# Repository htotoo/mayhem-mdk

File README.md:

# PortaPack Mayhem External Module Developer Kit "MDK"
This is the Developer Kit External Module for the [HackRF+PortaPack H4](https://github.com/portapack-mayhem/mayhem-firmware)

## How to get the hardware
All the design files are in the pcb folder. They are set up so you can let [JLCPCB](https://jlcpcb.com/) manufacture a few boards by using the files in pcb/production.

## How to compile
The software consists of two separate parts:
- The Standalone App that is uploaded and executed on the portapack.
  - This will be embedded in the the ESP32 firmware, so is required first.
  - The guide can be found [here](src/uart/Readme.md)
- The firmware for the ESP32-S3.
  - The guide can be found [here](src/portapack-external-module/README.md) 
  - Note: ESP-IDF version 5.4 introduced a breaking change in the I2C subsystem. So use the latest version of 5.3.

## How to use the example UART app
Once the Firmware is uploaded and the module is plugged into the Portapack, the UART app should appear in the Utilities menu.

The UART app will display any UART signal on pin 14.

## Schematics

## Pinout

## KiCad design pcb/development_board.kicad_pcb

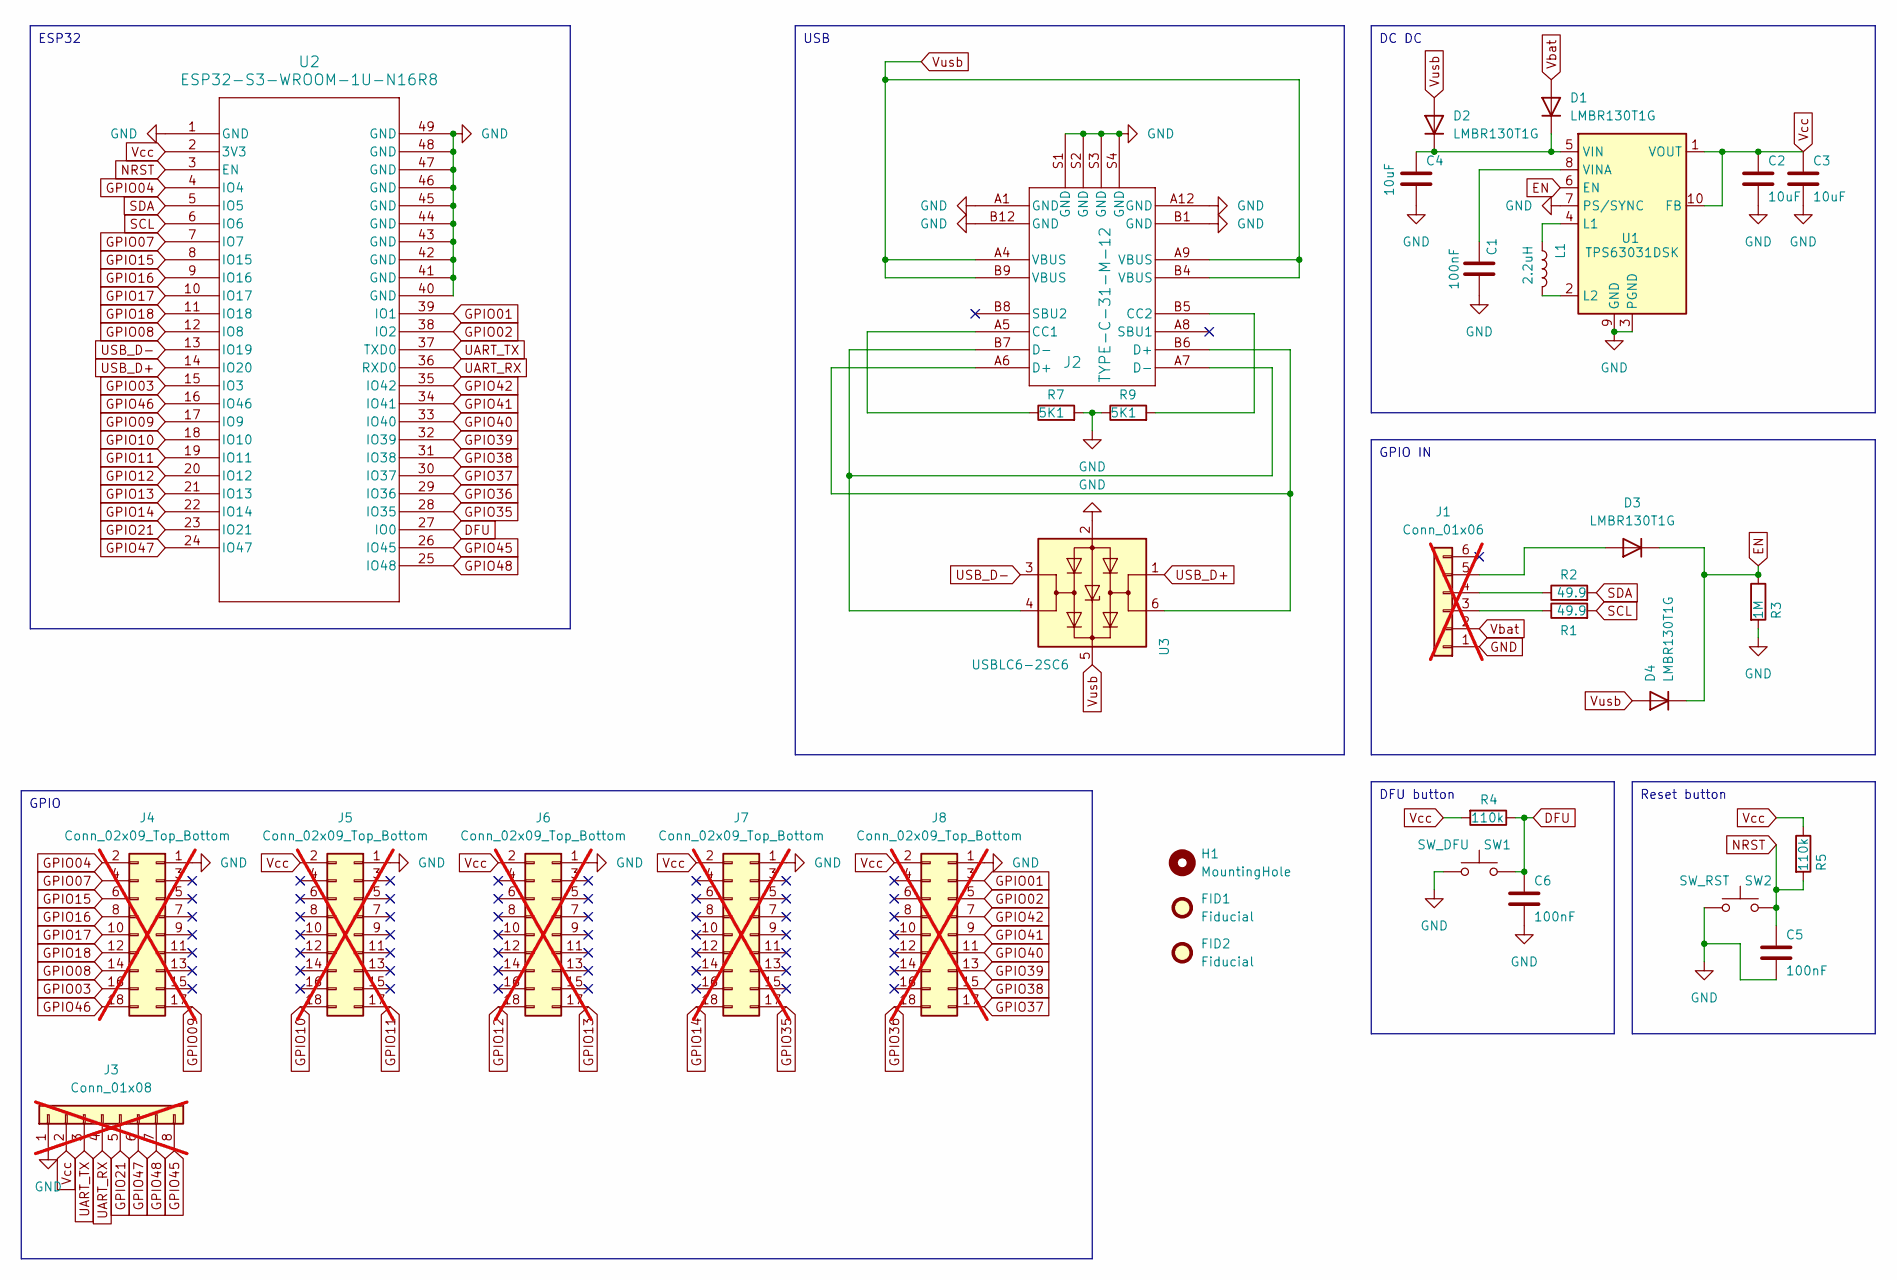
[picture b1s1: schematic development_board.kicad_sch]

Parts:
C1, C5, C6: 100nF; C_0402_1005Metric; Part CL05B104KO5NNNC; JLC 0402
C2, C3, C4: 10uF; C_0402_1005Metric; Part CL05A106MQ5NUNC; JLC 0402
D1, D2, D3, D4: LMBR130T1G; D_SOD-123; Part LMBR130T1G; JLC SOD-123
FID1, FID2: Fiducial; Fiducial_0.75mm_Mask1.5mm
H1: MountingHole; MountingHole_2mm
J1: Conn_01x06; External Module; not fitted
J2: TYPE-C-31-M-12; JLC SMD
J3: Conn_01x08; PinSocket_1x08_P2.54mm_Vertical; not fitted
J4, J5, J6, J7, J8: Conn_02x09_Top_Bottom; PinSocket_2x09_P2.54mm_Vertical; not fitted
L1: 2.2uH; L_Taiyo-Yuden_NR-40xx; Part NRS4010T2R2MDGGV; JLC SMD,4x4mm
R1, R2: 49.9; R_0402_1005Metric; Part 0402WGF499JTCE; JLC 0402
R3: 1M; R_0603_1608Metric; Part 0603WAF1004T5E; JLC 0603
R4, R5: 110k; R_0603_1608Metric; Part 0603WAF1103T5E; JLC 0603
R7, R9: 5K1; R_0603_1608Metric; Part 0603WAF5101T5E; JLC 0603
SW1: SW_DFU; SW_Push_1P1T_XKB_TS-1187A; Part TS-1187A-B-A-B; JLC SMD
SW2: SW_RST; SW_Push_1P1T_XKB_TS-1187A; Part TS-1187A-B-A-B; JLC SMD
U1: TPS63031DSK; WSON-10-1EP_2.5x2.5mm_P0.5mm_EP1.2x2mm; Part TPS63031DSKR; JLC SON-10-EP(2.5x2.5)
U2: ESP32-S3-WROOM-1U-N16R8; ESP32­S3­WROOM­1U_EXP; Part ESP32-S3-WROOM-1U-N16R8; JLC SMD,18x19.2mm
U3: USBLC6-2SC6; SOT-23-6; Part USBLC6-2SC6; JLC SOT-23-6

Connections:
DFU: C6.1, R4.1, SW1.2, U2.27 (IO0)
EN: D3.1 (K), D4.1 (K), R3.1, U1.6 (EN)
GND: C1.2, C2.2, C3.2, C4.2, C5.2, C6.2, J1.1, J2.A1 (GND), J2.A12 (GND), J2.B1 (GND), J2.B12 (GND), J2.S1 (GND), J2.S2 (GND), J2.S3 (GND), J2.S4 (GND), J3.1, J4.1, J5.1, J6.1, J7.1, J8.1, R3.2, R7.2, R9.1, SW1.1, SW2.1, U1.3 (PGND), U1.7 (PS/SYNC), U1.9 (GND), U1.11 (PGND), U2.1 (GND), U2.40 (GND), U2.41 (GND), U2.42 (GND), U2.43 (GND), U2.44 (GND), U2.45 (GND), U2.46 (GND), U2.47 (GND), U2.48 (GND), U2.49 (GND), U3.2 (GND)
GPIO01: J8.3, U2.39 (IO1)
GPIO02: J8.5, U2.38 (IO2)
GPIO03: J4.16, U2.15 (IO3)
GPIO04: J4.2, U2.4 (IO4)
GPIO07: J4.4, U2.7 (IO7)
GPIO08: J4.14, U2.12 (IO8)
GPIO09: J4.17, U2.17 (IO9)
GPIO10: J5.18, U2.18 (IO10)
GPIO11: J5.17, U2.19 (IO11)
GPIO12: J6.18, U2.20 (IO12)
GPIO13: J6.17, U2.21 (IO13)
GPIO14: J7.18, U2.22 (IO14)
GPIO15: J4.6, U2.8 (IO15)
GPIO16: J4.8, U2.9 (IO16)
GPIO17: J4.10, U2.10 (IO17)
GPIO18: J4.12, U2.11 (IO18)
GPIO21: J3.5, U2.23 (IO21)
GPIO35: J7.17, U2.28 (IO35)
GPIO36: J8.18, U2.29 (IO36)
GPIO37: J8.17, U2.30 (IO37)
GPIO38: J8.15, U2.31 (IO38)
GPIO39: J8.13, U2.32 (IO39)
GPIO40: J8.11, U2.33 (IO40)
GPIO41: J8.9, U2.34 (IO41)
GPIO42: J8.7, U2.35 (IO42)
GPIO45: J3.8, U2.26 (IO45)
GPIO46: J4.18, U2.16 (IO46)
GPIO47: J3.6, U2.24 (IO47)
GPIO48: J3.7, U2.25 (IO48)
NRST: C5.1, R5.2, SW2.2, U2.3 (EN)
unnamed: C4.1, D1.1 (K), D2.1 (K), U1.5 (VIN)
unnamed: D3.2 (A), J1.5
unnamed: J1.3, R1.1
unnamed: J1.4, R2.1
unnamed: J2.A5 (CC1), R7.1
unnamed: J2.B5 (CC2), R9.2
unnamed: J2.A6 (D+), J2.B6 (D+), U3.6 (I/O1)
unnamed: J2.A7 (D-), J2.B7 (D-), U3.4 (I/O2)
unnamed: L1.1, U1.4 (L1)
unnamed: L1.2, U1.2 (L2)
unnamed: C1.1, U1.8 (VINA)
SCL: R1.2, U2.6 (IO6)
SDA: R2.2, U2.5 (IO5)
UART_RX: J3.4, U2.36 (RXD0)
UART_TX: J3.3, U2.37 (TXD0)
USB_D+: U2.14 (IO20), U3.1 (I/O1)
USB_D-: U2.13 (IO19), U3.3 (I/O2)
Vbat: D1.2 (A), J1.2
Vcc: C2.1, C3.1, J3.2, J5.2, J6.2, J7.2, J8.2, R4.2, R5.1, U1.1 (VOUT), U1.10 (FB), U2.2 (3V3)
Vusb: D2.2 (A), D4.2 (A), J2.A4 (VBUS), J2.A9 (VBUS), J2.B4 (VBUS), J2.B9 (VBUS), U3.5 (VBUS)

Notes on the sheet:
GPIO IN
GPIO
USB
DFU button
ESP32
DC DC
Reset button

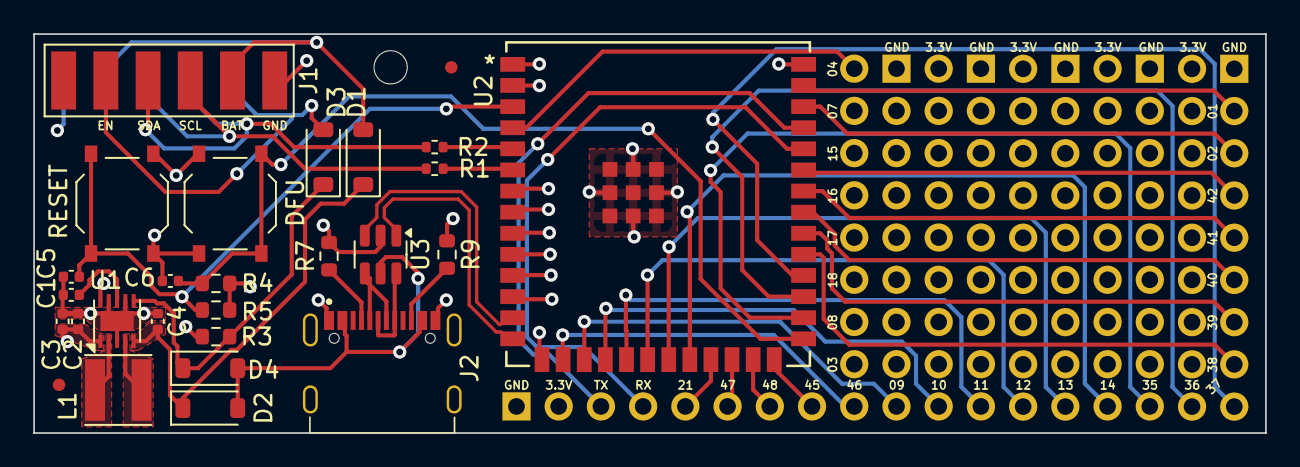
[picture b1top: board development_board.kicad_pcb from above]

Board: 4 copper layers, 74.1 x 24.0 mm, 34 parts (0 on the bottom side), 53 nets.

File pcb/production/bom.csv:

Designator,Footprint,Quantity,Value,LCSC Part #
"C1_5, C1_4, C1_3, C1_2, C1, C5_5, C5_4, C5_3, C5_2, C5, C6_5, C6_4, C6_3, C6_2, C6",0402,15,100nF,C1525
"C2_5, C2_4, C2_3, C2_2, C2, C3_5, C3_4, C3_3, C3_2, C3, C4_5, C4_4, C4_3, C4_2, C4",0402,15,10uF,C15525
"D1_5, D1_4, D1_3, D1_2, D1, D2_5, D2_4, D2_3, D2_2, D2, D3_5, D3_4, D3_3, D3_2, D3, D4_5, D4_4, D4_3, D4_2, D4",D_SOD-123,20,LMBR130T1G,C48974
"J2_5, J2_4, J2_3, J2_2, J2",TYPE-C-31-M-12,5,TYPE-C-31-M-12,C165948
"L1_5, L1_4, L1_3, L1_2, L1",L_Taiyo-Yuden_NR-40xx,5,2.2uH,C515383
"R1_5, R1_4, R1_3, R1_2, R1, R2_5, R2_4, R2_3, R2_2, R2",0402,10,49.9,C25120
"R3_5, R3_4, R3_3, R3_2, R3",0603,5,1M,C22935
"R4_5, R4_4, R4_3, R4_2, R4, R5_5, R5_4, R5_3, R5_2, R5",0603,10,110k,C25805
"R7_5, R7_4, R7_3, R7_2, R7, R9_5, R9_4, R9_3, R9_2, R9",0603,10,5K1,C23186
"SW1_5, SW1_4, SW1_3, SW1_2, SW1",SW_Push_1P1T_XKB_TS-1187A,5,SW_DFU,C318884
"SW2_5, SW2_4, SW2_3, SW2_2, SW2",SW_Push_1P1T_XKB_TS-1187A,5,SW_RST,C318884
"U1_5, U1_4, U1_3, U1_2, U1",WSON-10-1EP_2.5x2.5mm_P0.5mm_EP1.2x2mm,5,TPS63031DSK,C15516
"U2_5, U2_4, U2_3, U2_2, U2",ESP32­S3­WROOM­1U_EXP,5,ESP32-S3-WROOM-1U-N16R8,C3013946
"U3_5, U3_4, U3_3, U3_2, U3",SOT-23-6,5,USBLC6-2SC6,C2827654

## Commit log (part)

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2024-10-19 Added new commands. Now for placeholder.
2024-10-20 Refactor
2024-10-20 fix typo, add IRQ warning
2024-10-22 added sattrack app
2024-10-22 debug code
2024-10-22 stdmove
2024-10-22 sat-pre final
2024-10-23 ui fixes
2024-11-04 first
2024-11-04 graphical
2024-11-05 dr fixes
2024-11-06 added pcb design for mdk
2024-11-06 fixed labels
2024-11-06 fixed enable when running only on usb
2024-11-06 fixed parts selection
2024-11-08 I2C shell
2024-11-15 added panelized pcb
2024-12-10 stuff
2025-01-04 updated i2c slave driver
2025-02-05 updated i2c pins
2025-02-05 improved readme
2025-02-05 added uart app info
2025-02-05 fixed typo
2025-02-05 added vs code instructions
2025-08-28 initialdraft
2025-08-28 remove unenabled
2025-08-28 more
2025-08-28 added exit_app()
2025-09-01 mapdraw fix
2025-09-16 map compiles at least with common. this is just a backup
2025-09-16 more move
2025-09-16 fix cmake to create app and h every time
2025-09-16 readme updates
2025-09-16 updated to support v4 screen_width + height. updated ui.hpp to support UI_POS macros
2025-09-16 maybefix
2025-09-16 remove vscode dir
2025-09-16 remove vscode 2
2025-09-16 add vscode to gitignore
2025-10-10 a lot of changes, but not yet working
2025-10-10 debug
2025-10-10 it works with the next nightly. now the work can come
2025-10-11 aboutrain reworked to new nav format
2025-10-11 about memleak, and map rework
2025-10-11 much more impr
2025-10-11 more apps
2025-10-11 prepare wifi, better build
2025-10-11 theme
2025-10-11 wifi
2025-10-12 wifi_beta
2025-10-13 wifi settings app
2025-10-19 esp manager to set airplane mode
2025-10-29 tryfix
2025-10-30 espapps.
2025-10-30 fix keyboard bug
2025-10-30 revert delete
2025-10-31 tir test
2025-10-31 backup
2025-11-05 bool
2026-05-17 added jstarlink, and jdoorunlock
2026-05-17 comm
2026-05-17 icon for jstarlink
2026-05-17 idle miner
2026-05-17 added safecracker game
2026-05-18 retrorace
2026-05-18 logicagame
2026-05-18 more games
2026-05-18 bomber partly
2026-05-18 graphics
2026-05-18 fixes
2026-05-18 space fix
2026-05-18 improve build with collector
2026-05-18 fix text of blastzone
2026-05-18 fix iab hf
2026-05-18 typo
2026-05-18 fixed infinite jump game
2026-05-19 added signal router
2026-05-19 jnorad
2026-05-19 icon
2026-05-19 fix use after free hardfault
2026-05-19 added jtraffic app
2026-05-20 jgrid
2026-05-20 fix focus on startup.
2026-05-20 pos fix of jgrid
2026-05-20 Fix use after free, and fix the focus problems. Added output collector for mass building.
2026-05-20 fix typo
2026-06-01 ACube
2026-06-01 awarp
2026-06-01 AWormhole
2026-06-01 more animations
2026-06-01 sokoban
2026-06-01 ahal
2026-06-01 fix color
2026-06-16 fix anim crash on exit
2026-06-18 Fix use after free, and fix the focus problems. Added output collector for mass building. (#22)
    * Fix use after free, and fix the focus problems. Added output collector for mass building.
    * fix typo
2026-06-19 update geomap
2026-06-19 geomapfix
2026-06-19 partlyfix
2026-06-19 map apps
